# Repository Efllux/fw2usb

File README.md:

# fw2usb: an open FireWire → USB adapter

Apple removed FireWire from macOS, Thunderbolt-to-FireWire dongles are discontinued, and
USB-C laptops never had it. Meanwhile there are thousands of excellent FireWire audio
interfaces, DV cameras and drives collecting dust.

**fw2usb is an open-hardware, open-source adapter that makes a FireWire device show up as a
normal USB device.** No Linux computer hidden in a box, no Thunderbolt dongle chain, no kernel
driver on your computer.

```
FireWire device ─ FW400/800 ─▶ [ PHY chip ─ FPGA link layer ─ USB 2.0 HS ] ─ USB-C ─▶ Mac / PC / Linux
```

- **Audio interfaces across all families** (BeBoB, DICE, Oxford, Fireworks, MOTU, RME, Digi, TASCAM and generic AV/C): the adapter presents itself as a
  class-compliant USB Audio 2.0 device, so it works with the OS's built-in driver.
- **Universal "raw link" mode**: FireWire packets tunnelled over USB to an open Rust host
  library, so disks, DV cameras and other devices can be supported in user-space software.

Three tiers: class-compliant UAC2 async audio out of the box; an always-present
companion interface for mixer/routing/configuration; and an explicit persistent
switch to a different USB PID for raw FireWire tunneling. Hold the button at plug-in
for audio-mode recovery. Profiles and signed DFU updates are planned; none of these
USB personalities is implemented yet. See [architecture](docs/DESIGN.md).

## Status

🧪 **Early: design + protocol core. No working hardware yet.** This is the best moment to
join and shape it.

| Piece | State |
|---|---|
| [Design](docs/DESIGN.md) | first draft |
| `crates/fw-amdtp` (audio packet format, timing) | ✅ tested |
| `crates/fw-phy-model` (soft-PHY research model) | ✅ tested, early |
| `gateware/` (FPGA 1394 link layer) | not started |
| `host/` (Rust host tools) | not started |
| `hardware/` (PCB) | not started |

See the [roadmap](ROADMAP.md) and the [device list](docs/DEVICES.md).

## How you can help

You don't need to be an FPGA wizard. We need:
- **People with FireWire devices** who can capture traffic or test builds → add yours to [DEVICES.md](docs/DEVICES.md)
- **FPGA / HDL** folks (link layer, USB ULPI)
- **Rust** developers (protocol, host tools, firmware)
- **PCB designers** (the eventual dongle)
- **Protocol archaeologists**: AV/C, BeBoB, DICE, SBP-2 know-how

Start with [CONTRIBUTING.md](CONTRIBUTING.md).

## Licensing

- Software, firmware and gateware: **MIT OR Apache-2.0**
- Hardware designs (`hardware/`): **CERN-OHL-S v2** (strongly reciprocal: anyone may build and sell adapters, but modified designs must be published under the same licence)

## Building

```sh
cargo test
```

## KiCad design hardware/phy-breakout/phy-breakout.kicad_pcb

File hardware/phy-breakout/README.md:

# FireWire PHY breakout, revision 0.2

One FireWire 400 (6-pin) port and a TI TSB41BA3F-EP PHY, cabled to an FPGA
board through a 2x10 header. It exists for milestone M1: bus reset, self-ID
and reading the configuration ROM of a real device.

**Status.** Schematic and 4-layer board are complete and checked with KiCad
8.0.9: ERC 0 errors and warnings; DRC 0 violations, 0 unconnected items,
0 schematic-parity issues, with no exclusions. Fabrication files are in
`fab/`. **No board has been built or tested.** Before ordering, read
"Check before ordering" below.

Why this PHY, how it differs from the TSB41AB2 the gateware was written
against, the gateware changes that follow, and every schematic value with
its datasheet page are in [REVIEW.md](REVIEW.md).

## What is on the board

- U1 TSB41BA3F-EP, PHY-LINK interface in 1394a mode (BMODE low), 49.152 MHz
  crystal, internal core regulators, single 3.3 V supply.
- Strap mode 3 (S5=0, S4=1, S3=0): ports 2 and 1 are data-strobe only, port 0
  is bilingual. Only port 2 is used. Power class 000.
- J1 FireWire 400 receptacle on port 2, with 56.2 Ohm termination, 1 uF on
  TPBIAS, 4.99 kOhm and 270 pF on the TPB midpoint, and a TPD4E05U06 ESD
  array next to the connector. Shield goes to ground through 1 MOhm, 10 nF
  and 1 nF in parallel.
- Cable power is **not connected** in either direction. A bus-powered device
  needs its own power supply.
- J2 2x10 header: the PHY-LINK bus with 22 Ohm in series on the clock, D0-D7,
  CTL0-CTL1 and LREQ, 1 kOhm in series on LPS and LinkOn, and a 10 kOhm
  pull-down on LPS so the interface stays off until the FPGA drives it.
- J3 two-pin 3.3 V supply input. There is no regulator and no reverse-polarity
  protection: use a current-limited bench supply, 3.0 to 3.6 V, 200 mA.
  The PHY draws 110 mA typical, 150 mA maximum.

## J2 header

Odd pins are the column nearer the board edge; pin 1 is square and marked.
In a ribbon cable the clock and LREQ each lie between two ground wires.
The ULX3S column is the wiring plan from `gateware/README.md`; those are
silkscreen net names on the ULX3S, not connector positions. Keep the cable
short (10 cm or less) or use a small adapter board.

| J2 pin | Signal | ULX3S net | | J2 pin | Signal | ULX3S net |
|---|---|---|---|---|---|---|
| 1 | GND | GND | | 2 | RESET_N, open drain, active low | GP7 |
| 3 | LinkOn (from PHY) | GN6 | | 4 | LPS (to PHY) | GP6 |
| 5 | GND | GND | | 6 | LREQ | GN5 |
| 7 | GND | GND | | 8 | SCLK 49.152 MHz (from PHY) | GP0 |
| 9 | GND | GND | | 10 | CTL0 | GN4 |
| 11 | D0 | GN0 | | 12 | CTL1 | GP5 |
| 13 | D2 | GN1 | | 14 | D1 | GP1 |
| 15 | D4 | GN2 | | 16 | D3 | GP2 |
| 17 | D6 | GN3 | | 18 | D5 | GP3 |
| 19 | GND | GND | | 20 | D7 | GP4 |

This pin order is new in revision 0.2 (it lets the bus route on one layer
without crossings). There is no 3.3 V pin on J2. The grounds of the two
boards are common; the link is not isolated.

FPGA side: 3.3 V LVCMOS, lowest drive strength and slow slew on outputs.
RESET_N must be driven low or left floating, never driven high; hold it low
for at least 2 ms after the supply and clock are stable. Keep D, CTL and
LREQ undriven until the PHY has finished its interface start-up.

## Board

- 57.8 x 32.6 mm, 4 layers, 1.6 mm, four 3.2 mm mounting holes.
- Layers: top signals and parts; inner 1 unbroken ground; inner 2 3.3 V plane
  (the digital core rail is a 0.4 mm track on this layer); bottom ground fill
  and the decoupling capacitors, placed under the PHY pin rows.
- Cable pairs: top layer only, no vias, over unbroken ground, 12.43 mm from
  PHY pin to connector pad, both lines of each pair the same length. Lines
  0.22 mm, gap 0.28 mm. With 0.21 mm of 7628 prepreg (dielectric constant
  4.4) to the ground layer the usual microstrip formulas give about 110 Ohm
  differential. This is calculated, not measured.
- PHY-LINK bus: top layer only, no vias, 0.2 mm lines over ground. Lengths
  from PHY pin to header pin are 14.7 to 19.8 mm, a spread of 5.1 mm or
  about 35 ps, against a 20.3 ns clock period (`reports/lengths.txt`).
- U1 thermal pad: 6 x 6 mm land with 25 vias to the ground plane; ground
  pins run straight into the land.

### Board-house rules used

Checked against JLCPCB's published 4-layer limits (read 2026-11-13), with
margin. PCBWay's standard 4-layer service has similar limits.

| | This board | JLCPCB limit |
|---|---|---|
| Track width | 0.2 mm minimum used | 0.09 mm |
| Copper spacing | 0.15 mm net-class rule, 0.127 mm absolute | 0.09 mm |
| Via | 0.3 mm hole, 0.5 mm pad (0.6 mm in the thermal land) | 0.15 / 0.25 mm |
| Via hole to other copper | 0.2 mm | 0.2 mm |
| Hole to hole | 0.25 mm | 0.2 mm |
| Copper to board edge | 0.3 mm | 0.2 mm |
| Plated slots | 1.0 x 2.5 mm | 0.35 mm wide |
| Silkscreen | 1.0 mm text, 0.15 mm lines | 1.0 mm, 0.15 mm |

Order as: 4 layers, 1.6 mm, 1 oz outer copper, a stackup with 7628 prepreg
(about 0.2 mm) under the outer layers, any finish (ENIG is easier for hand
soldering the 0.5 mm pitch parts).

## Check before ordering

1. **U1 stock and price.** ti.com listed the part as active at about $54 to
   $72 on 2026-11-12; stock was not verified.
2. **J1 part in hand.** The footprint is the land pattern of Keystone 927TR,
   which the Assmann WSW A-IES-SMT-U/R drawing matches. The Keystone drawing
   gives the pad numbering used here. If the Assmann part is bought, check
   with a continuity meter that pads 1 to 6 reach contacts 1 to 6.
3. **Stackup.** Confirm the prepreg thickness in the order form. A much
   thinner prepreg lowers the pair impedance.

## Assembly notes

- 71 parts: 46 on top, 25 capacitors on the bottom. Mostly 0402.
- U1 and U2 are 0.5 mm pitch. U1 has an exposed pad that must be soldered:
  use paste and hot air or a hotplate; an iron alone cannot reach it.
- Solder the bottom capacitors first, then the top.
- `fab/assembly/` has the BOM, the placement file and drawings of both sides.

- Part numbers for resistors, capacitors, headers and the crystal are
  candidates and were not checked for stock. Any part with the same value,
  package and dielectric will do; the crystal must be a 49.152 MHz
  fundamental-mode part.

## Cost estimate

Estimates, not quotes; nothing was ordered.

| Item | Estimate |
|---|---|
| Five bare boards, JLCPCB 4-layer, before shipping | $10 to $30 |
| U1 TSB41BA3F-EP (ti.com list price) | $54 to $72 |
| J1, U2, crystal, headers | about $6 |
| 65 resistors and capacitors | about $3 |
| **Parts for one board** | **about $65 to $80** |

The PHY is most of the parts cost.

## After assembly: measurements still needed

| What | How |
|---|---|
| Crystal load capacitors C6, C7 | Frequency counter on J2 pin 8 with LPS high: 49.152 MHz within 100 ppm. Raise both capacitors if high, lower if low. |
| Reset time | Scope RESET_N against 3.3 V at power-up: low for at least 2 ms after the supply is valid. |
| Supply current | About 110 mA with a device connected. |
| TPBIAS | 1.67 to 2.02 V on C2 with a cable connected. |
| Bus signal quality | Scope SCLK, one data line and LREQ at the FPGA end of the real cable. Adjust the 22 Ohm resistors or FPGA drive strength if they ring. |
| Pair impedance | Only if S400 traffic shows errors: time-domain reflectometer, or order with impedance control. |

ESD and cable-fault behaviour cannot be tested on the bench. Treat the port
as protected against handling, not against miswired cables.

## Rebuilding

Everything except the two documents is generated. With KiCad 8.0.9:

```
tools/build.sh /Applications/KiCad/KiCad.app
```

This runs `tools/design.py` (net list, placement, BOM), `tools/schematic.py`
(schematic and symbol library), `tools/pcb.py` (footprints, placement, all
routing, zones, project rules), then ERC and DRC into `reports/`, then the
fabrication files into `fab/`. The scripts need the Python that ships inside
KiCad. KiCad does not have to be installed: the official disk image can be
mounted and the path to `KiCad.app` inside it given to the script. The
official 8.0.9 image has SHA-256
`865a96ff02e9dc4d5e6d3554d8224b7d780aae7b2975329d911dfe57820ba07a`.

A rebuild gives the same geometry and the same check results, but KiCad
assigns new internal identifiers to board items, so the board, footprint and
Gerber files differ textually from the committed ones.

No autorouter is used. To change the layout, edit the coordinates in
`design.py` and the routes in `pcb.py`, rebuild, and read `reports/drc.txt`.

The schematic is a labelled-pin drawing of the net list, not a drawn
circuit diagram. It is correct for ERC and for the parity check against the
board, but it is hard to read; REVIEW.md describes the circuit.

## Files

| | |
|---|---|
| `REVIEW.md` | PHY choice, gateware changes implied, datasheet citations |
| `tools/` | generator scripts and `build.sh` |
| `design.json`, `BOM.csv` | generated net list and grouped BOM |
| `phy-breakout.kicad_sch`, `.kicad_pcb`, `.kicad_pro` | KiCad 8 project |
| `fw2usb.kicad_sym`, `fw2usb.pretty/` | generated symbols and footprints |
| `reports/` | ERC, DRC and routed-length reports |
| `fab/gerbers/` | Gerbers and drill files for the board house |
| `fab/assembly/` | BOM, pick-and-place, assembly drawings |

No vendor CAD, datasheet or other third-party file is stored here. Hardware
licence: CERN-OHL-S v2.

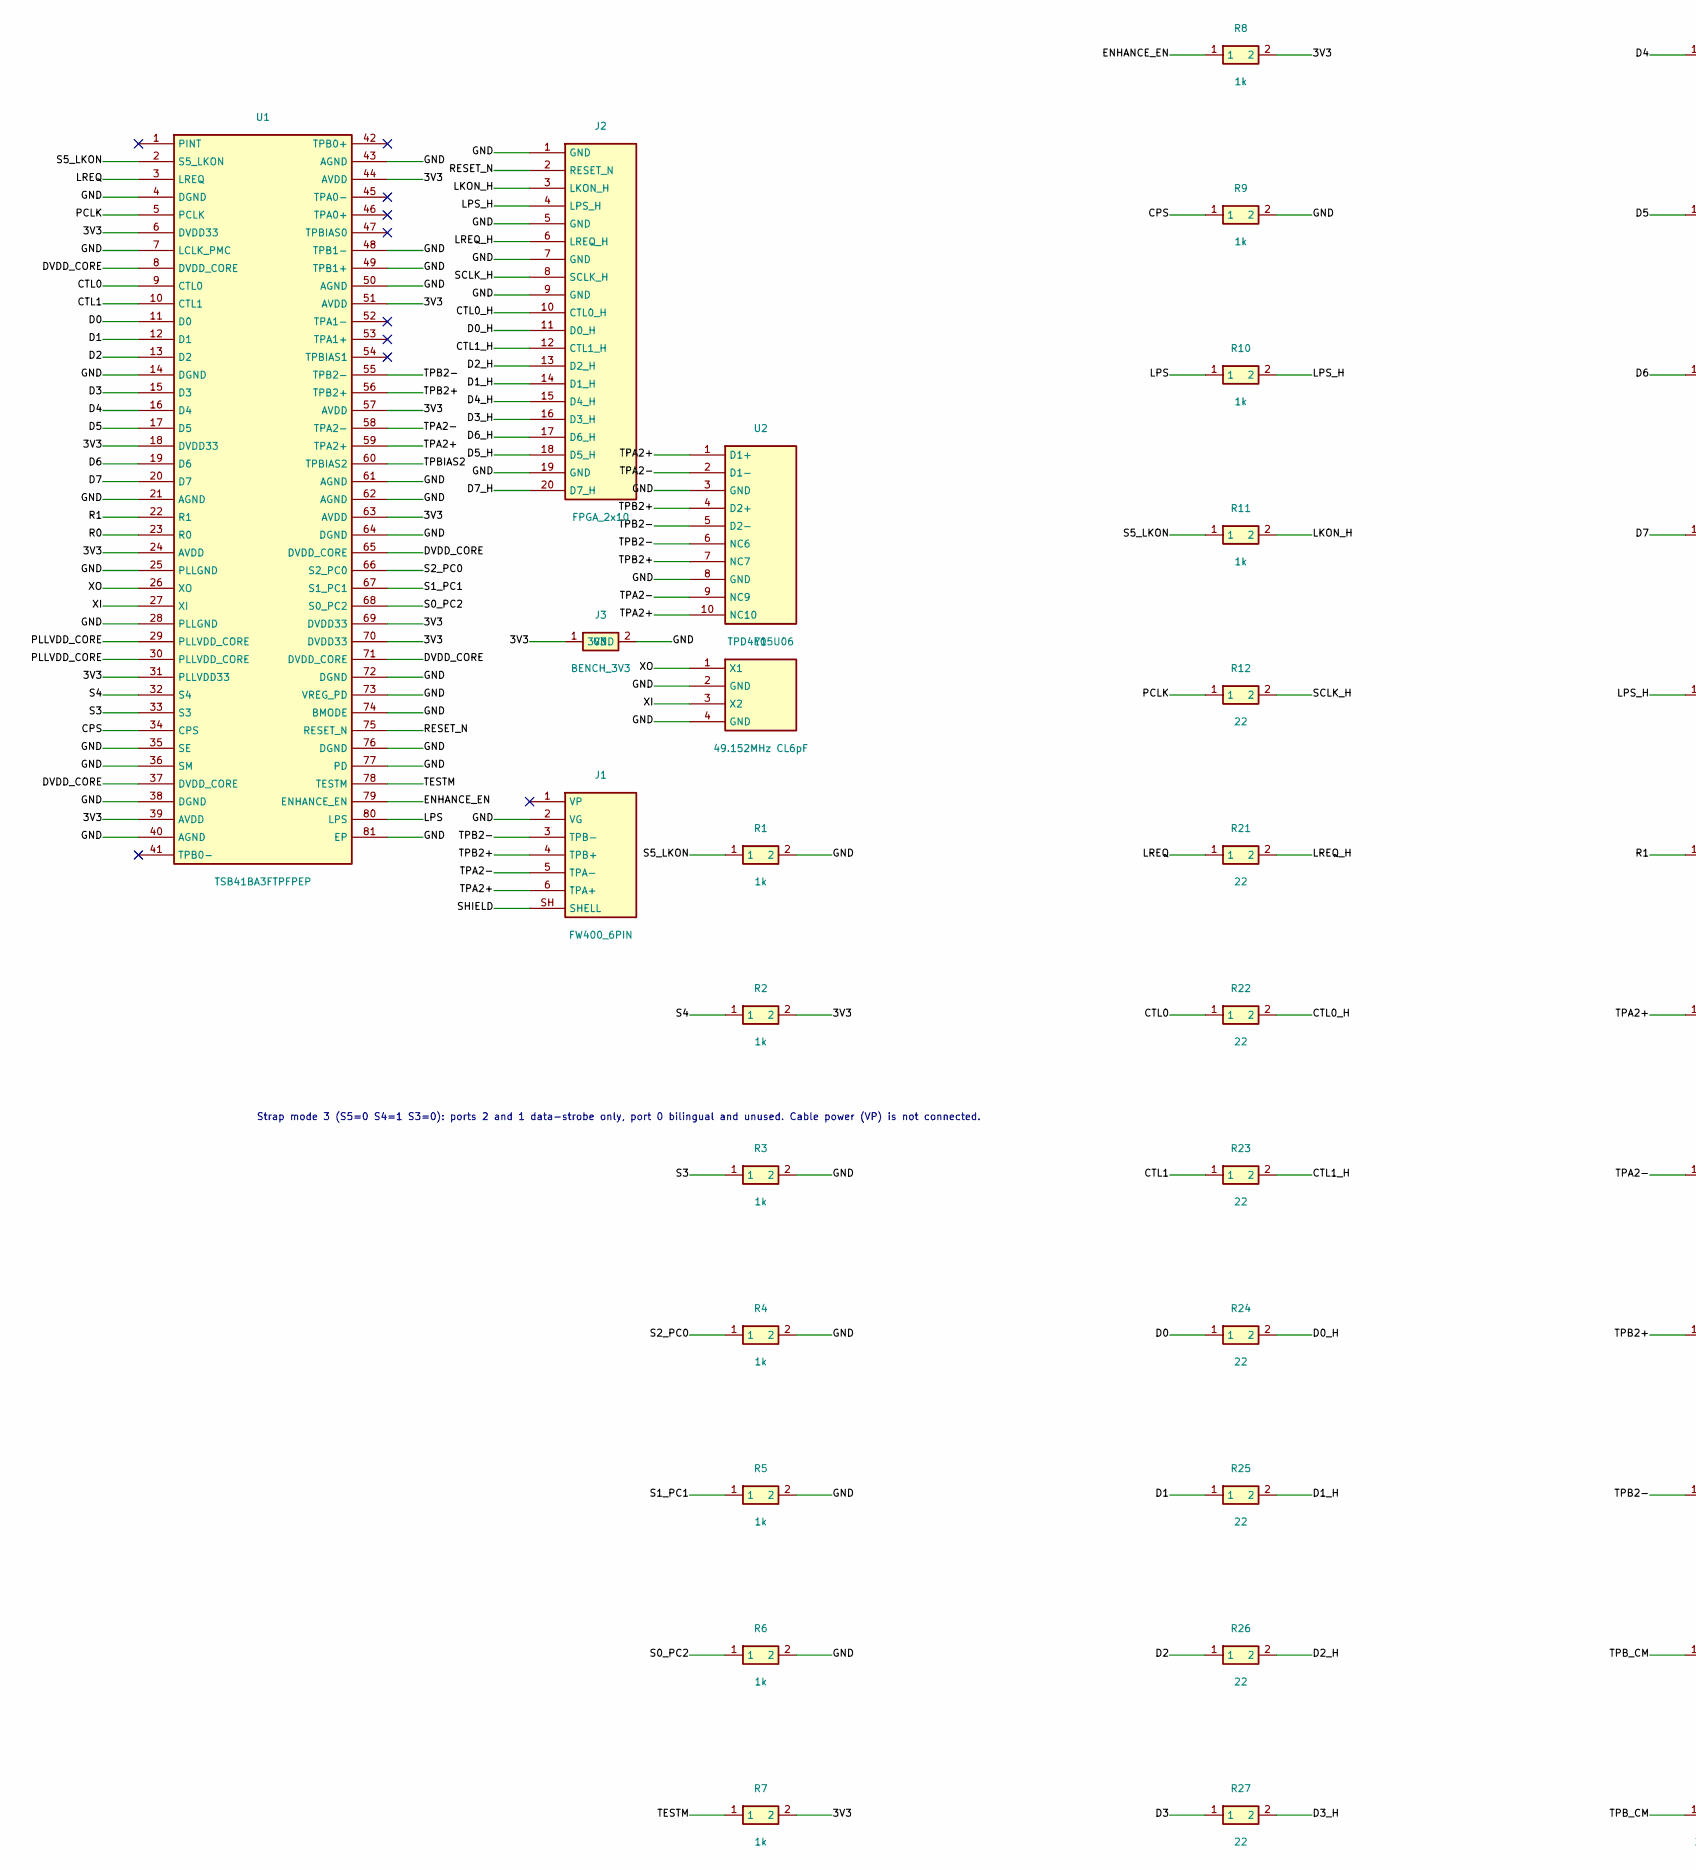
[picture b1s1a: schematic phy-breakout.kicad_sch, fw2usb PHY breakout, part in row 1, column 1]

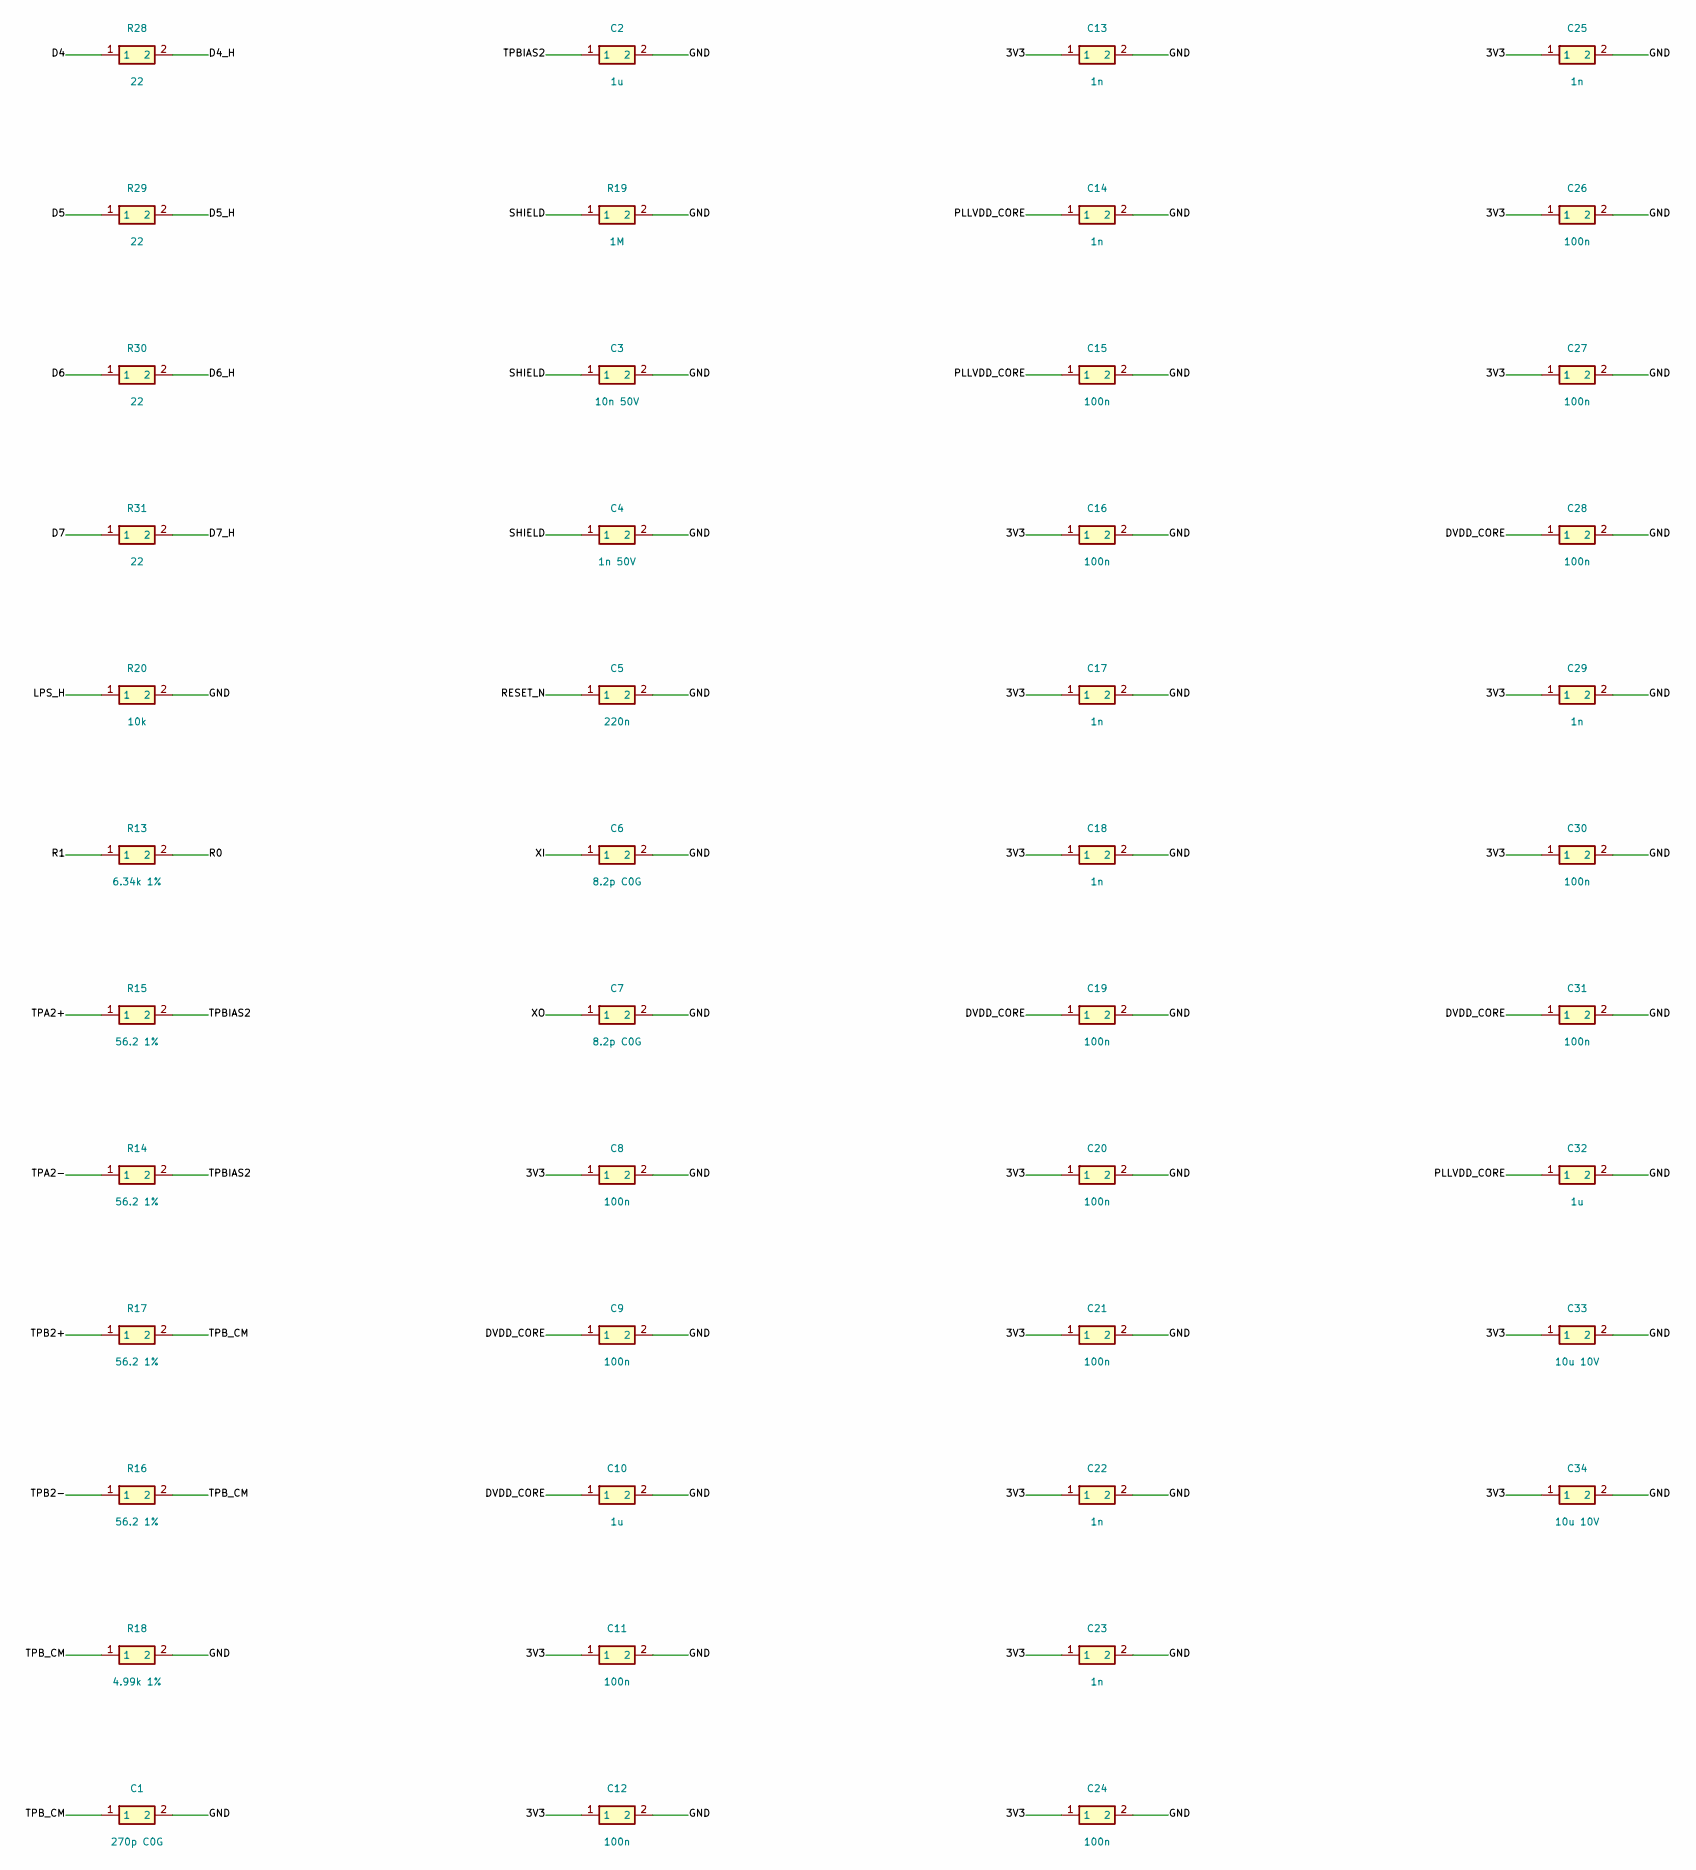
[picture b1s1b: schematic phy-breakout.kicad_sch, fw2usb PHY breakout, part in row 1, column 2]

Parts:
C1: 270p C0G; C; MPN Murata GRM1555C1H271JA01D
C2, C10, C32: 1u; C; MPN Murata GRM155R61A105KE15D
C3: 10n 50V; C0603; MPN Murata GRM188R71H103KA01D
C4: 1n 50V; C0603; MPN Murata GRM1885C1H102JA01D
C5: 220n; C; MPN Murata GRM155R71C224KA12D
C6, C7: 8.2p C0G; C; MPN Murata GRM1555C1H8R2DA01D
C8, C9, C11, C12, C15, C16, C19, C20, C21, C24, C26, C27, C28, C30, C31: 100n; C; MPN Murata GRM155R71C104KA88D
C13, C14, C17, C18, C22, C23, C25, C29: 1n; C; MPN Murata GRM1555C1H102JA01D
C33, C34: 10u 10V; C0805; MPN Murata GRM21BR61A106KE19L
J1: FW400_6PIN; FW6SMT; MPN Keystone 927TR
J2: FPGA_2x10; Header20; MPN Samtec TSW-110-07-G-D
J3: BENCH_3V3; Header2; MPN Samtec TSW-102-07-G-S
R1, R2, R3, R4, R5, R6, R7, R8, R9, R10, R11: 1k; R; MPN Yageo RC0402FR-071KL
R12, R21, R22, R23, R24, R25, R26, R27, R28, R29, R30, R31: 22; R; MPN Yageo RC0402FR-0722RL
R13: 6.34k 1%; R; MPN Yageo RC0402FR-076K34L
R14, R15, R16, R17: 56.2 1%; R; MPN Yageo RC0402FR-0756R2L
R18: 4.99k 1%; R; MPN Yageo RC0402FR-074K99L
R19: 1M; R0603; MPN Yageo RC0603FR-071ML
R20: 10k; R; MPN Yageo RC0402FR-0710KL
U1: TSB41BA3FTPFPEP; HTQFP80; MPN TI TSB41BA3FTPFPEP
U2: TPD4E05U06; USON10; MPN TI TPD4E05U06DQAR
Y1: 49.152MHz CL6pF; Crystal4; MPN Abracon ABM8W-49.1520MHZ-6-K1Z-T3

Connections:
/3V3: C8.1, C11.1, C12.1, C13.1, C16.1, C17.1, C18.1, C20.1, C21.1, C22.1, C23.1, C24.1, C25.1, C26.1, C27.1, C29.1, C30.1, C33.1, C34.1, J3.1 (3V3), R2.2, R7.2, R8.2, U1.6 (DVDD33), U1.18 (DVDD33), U1.24 (AVDD), U1.31 (PLLVDD33), U1.39 (AVDD), U1.44 (AVDD), U1.51 (AVDD), U1.57 (AVDD), U1.63 (AVDD), U1.69 (DVDD33), U1.70 (DVDD33)
/CPS: R9.1, U1.34 (CPS)
/CTL0: R22.1, U1.9 (CTL0)
/CTL0_H: J2.10 (CTL0_H), R22.2
/CTL1: R23.1, U1.10 (CTL1)
/CTL1_H: J2.12 (CTL1_H), R23.2
/D0: R24.1, U1.11 (D0)
/D0_H: J2.11 (D0_H), R24.2
/D1: R25.1, U1.12 (D1)
/D1_H: J2.14 (D1_H), R25.2
/D2: R26.1, U1.13 (D2)
/D2_H: J2.13 (D2_H), R26.2
/D3: R27.1, U1.15 (D3)
/D3_H: J2.16 (D3_H), R27.2
/D4: R28.1, U1.16 (D4)
/D4_H: J2.15 (D4_H), R28.2
/D5: R29.1, U1.17 (D5)
/D5_H: J2.18 (D5_H), R29.2
/D6: R30.1, U1.19 (D6)
/D6_H: J2.17 (D6_H), R30.2
/D7: R31.1, U1.20 (D7)
/D7_H: J2.20 (D7_H), R31.2
/DVDD_CORE: C9.1, C10.1, C19.1, C28.1, C31.1, U1.8 (DVDD_CORE), U1.37 (DVDD_CORE), U1.65 (DVDD_CORE), U1.71 (DVDD_CORE)
/ENHANCE_EN: R8.1, U1.79 (ENHANCE_EN)
/GND: C1.2, C2.2, C3.2, C4.2, C5.2, C6.2, C7.2, C8.2, C9.2, C10.2, C11.2, C12.2, C13.2, C14.2, C15.2, C16.2, C17.2, C18.2, C19.2, C20.2, C21.2, C22.2, C23.2, C24.2, C25.2, C26.2, C27.2, C28.2, C29.2, C30.2, C31.2, C32.2, C33.2, C34.2, J1.2 (VG), J2.1 (GND), J2.5 (GND), J2.7 (GND), J2.9 (GND), J2.19 (GND), J3.2 (GND), R1.2, R3.2, R4.2, R5.2, R6.2, R9.2, R18.2, R19.2, R20.2, U1.4 (DGND), U1.7 (LCLK_PMC), U1.14 (DGND), U1.21 (AGND), U1.25 (PLLGND), U1.28 (PLLGND), U1.35 (SE), U1.36 (SM), U1.38 (DGND), U1.40 (AGND), U1.43 (AGND), U1.48 (TPB1-), U1.49 (TPB1+), U1.50 (AGND), U1.61 (AGND), U1.62 (AGND), U1.64 (DGND), U1.72 (DGND), U1.73 (VREG_PD), U1.74 (BMODE), U1.76 (DGND), U1.77 (PD), U1.81 (EP), U2.3 (GND), U2.8 (GND), Y1.2 (GND), Y1.4 (GND)
/LKON_H: J2.3 (LKON_H), R11.2
/LPS: R10.1, U1.80 (LPS)
/LPS_H: J2.4 (LPS_H), R10.2, R20.1
/LREQ: R21.1, U1.3 (LREQ)
/LREQ_H: J2.6 (LREQ_H), R21.2
/PCLK: R12.1, U1.5 (PCLK)
/PLLVDD_CORE: C14.1, C15.1, C32.1, U1.29 (PLLVDD_CORE), U1.30 (PLLVDD_CORE)
/R0: R13.2, U1.23 (R0)
/R1: R13.1, U1.22 (R1)
/RESET_N: C5.1, J2.2 (RESET_N), U1.75 (RESET_N)
/S0_PC2: R6.1, U1.68 (S0_PC2)
/S1_PC1: R5.1, U1.67 (S1_PC1)
/S2_PC0: R4.1, U1.66 (S2_PC0)
/S3: R3.1, U1.33 (S3)
/S4: R2.1, U1.32 (S4)
/S5_LKON: R1.1, R11.1, U1.2 (S5_LKON)
/SCLK_H: J2.8 (SCLK_H), R12.2
/SHIELD: C3.1, C4.1, J1.SH (SHELL), R19.1
/TESTM: R7.1, U1.78 (TESTM)
/TPA2+: J1.6 (TPA+), R15.1, U1.59 (TPA2+), U2.1 (D1+), U2.10 (NC10)
/TPA2-: J1.5 (TPA-), R14.1, U1.58 (TPA2-), U2.2 (D1-), U2.9 (NC9)
/TPB2+: J1.4 (TPB+), R17.1, U1.56 (TPB2+), U2.4 (D2+), U2.7 (NC7)
/TPB2-: J1.3 (TPB-), R16.1, U1.55 (TPB2-), U2.5 (D2-), U2.6 (NC6)
/TPBIAS2: C2.1, R14.2, R15.2, U1.60 (TPBIAS2)
/TPB_CM: C1.1, R16.2, R17.2, R18.1
/XI: C6.1, U1.27 (XI), Y1.3 (X2)
/XO: C7.1, U1.26 (XO), Y1.1 (X1)

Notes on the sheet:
Strap mode 3 (S5=0 S4=1 S3=0): ports 2 and 1 data-strobe only, port 0 bilingual and unused. Cable power (VP) is not connected.

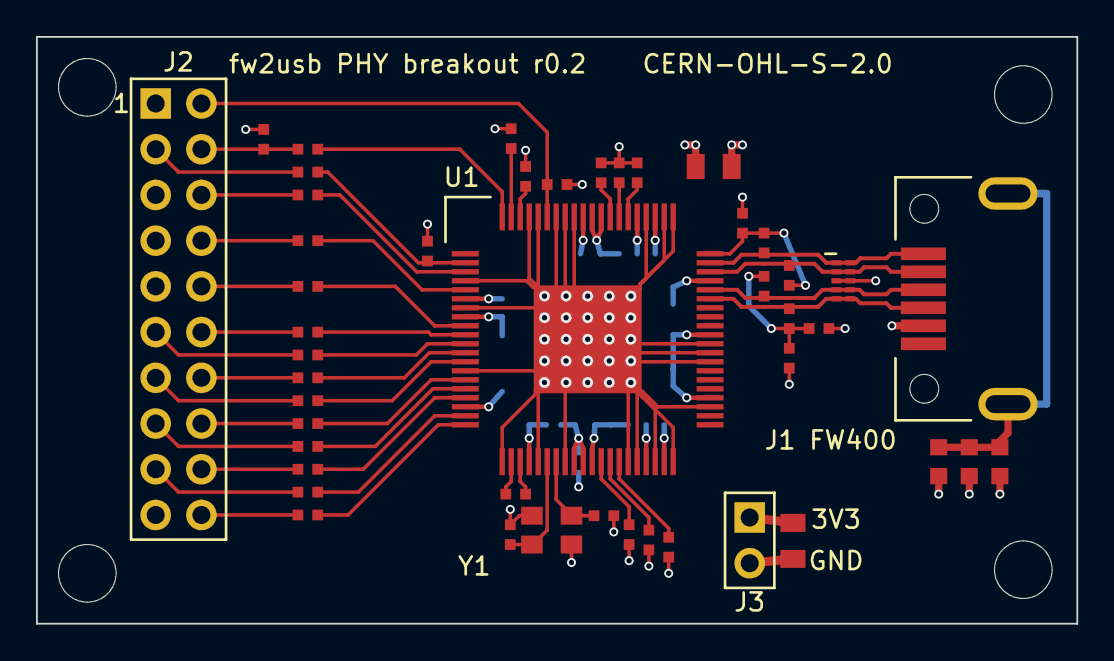
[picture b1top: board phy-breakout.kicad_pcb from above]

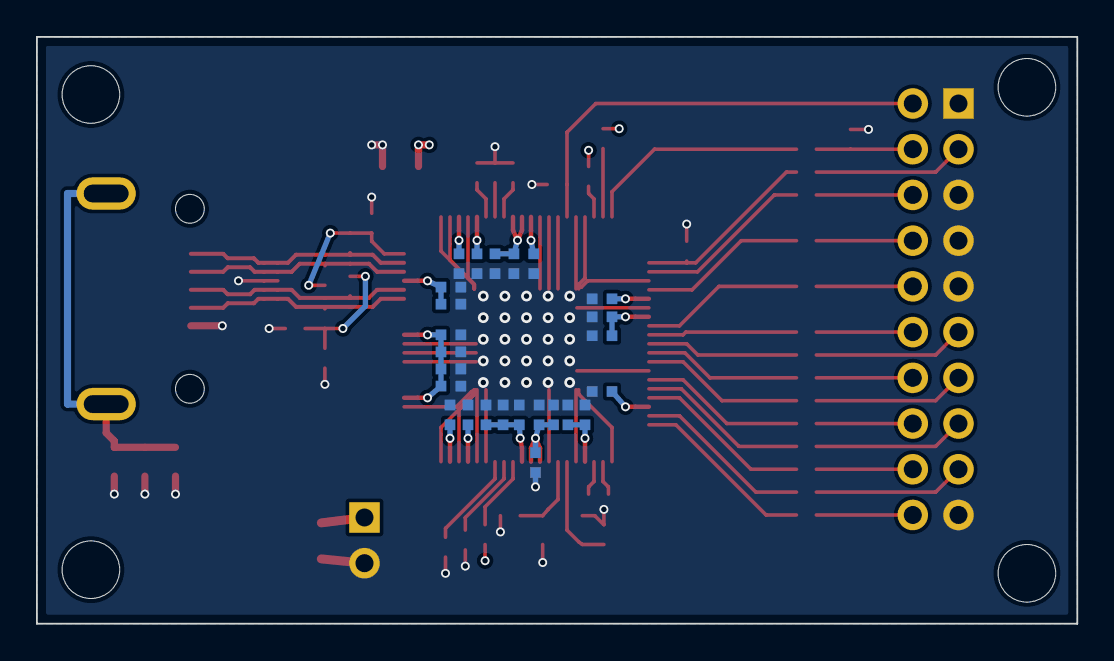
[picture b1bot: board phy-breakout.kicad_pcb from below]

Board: 4 copper layers, 57.8 x 32.6 mm, 75 parts (25 on the bottom side), 52 nets.

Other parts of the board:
H1, H2, H3, H4: M3; MH3

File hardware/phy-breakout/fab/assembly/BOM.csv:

References,Qty,Value,Package,Manufacturer part,Side,Note
U1,1,TSB41BA3FTPFPEP,"HTQFP-80 12x12 mm 0.5 mm pitch, 6x6 mm pad",TI TSB41BA3FTPFPEP,top,check stock and price before ordering; see REVIEW.md
J2,1,FPGA_2x10,2x10 2.54 mm,Samtec TSW-110-07-G-D,top,any 2x10 2.54 mm header
J3,1,BENCH_3V3,1x2 2.54 mm,Samtec TSW-102-07-G-S,top,"regulated 3.3 V, 200 mA or more"
J1,1,FW400_6PIN,IEEE 1394 6-pin right-angle SMT,Keystone 927TR,top,second source Assmann WSW A-IES-SMT-U/R: check its pad order by continuity first
U2,1,TPD4E05U06,USON-10 2.5x1.0 mm,TI TPD4E05U06DQAR,top,
Y1,1,49.152MHz CL6pF,3.2x2.5 mm 4-pad,Abracon ABM8W-49.1520MHZ-6-K1Z-T3,top,"any 49.152 MHz fundamental 3225 crystal, 30 ppm; recalculate C6/C7 for its load"
R1 R2 R3 R4 R5 R6 R7 R8 R9 R10 R11,11,1k,0402,Yageo RC0402FR-071KL,top,
R12 R21 R22 R23 R24 R25 R26 R27 R28 R29 R30 R31,12,22,0402,Yageo RC0402FR-0722RL,top,
R20,1,10k,0402,Yageo RC0402FR-0710KL,top,
R13,1,6.34k 1%,0402,Yageo RC0402FR-076K34L,top,
R15 R14 R17 R16,4,56.2 1%,0402,Yageo RC0402FR-0756R2L,top,
R18,1,4.99k 1%,0402,Yageo RC0402FR-074K99L,top,
C1,1,270p C0G,0402,Murata GRM1555C1H271JA01D,top,
C2 C10 C32,3,1u,0402,Murata GRM155R61A105KE15D,both,
R19,1,1M,0603,Yageo RC0603FR-071ML,top,
C3,1,10n 50V,0603,Murata GRM188R71H103KA01D,top,
C4,1,1n 50V,0603,Murata GRM1885C1H102JA01D,top,
C5,1,220n,0402,Murata GRM155R71C224KA12D,top,"measure reset low time at power-up, 2 ms minimum"
C6 C7,2,8.2p C0G,0402,Murata GRM1555C1H8R2DA01D,top,keep equal to C6; trim so that PCLK is 49.152 MHz within 100 ppm
C8 C9 C11 C12 C15 C16 C19 C20 C21 C24 C26 C27 C28 C30 C31,15,100n,0402,Murata GRM155R71C104KA88D,bottom,
C13 C14 C17 C18 C22 C23 C25 C29,8,1n,0402,Murata GRM1555C1H102JA01D,bottom,
C33 C34,2,10u 10V,0805,Murata GRM21BR61A106KE19L,top,

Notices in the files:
hardware/phy-breakout/phy-breakout.kicad_pcb:
CERN-OHL-S-2.0
